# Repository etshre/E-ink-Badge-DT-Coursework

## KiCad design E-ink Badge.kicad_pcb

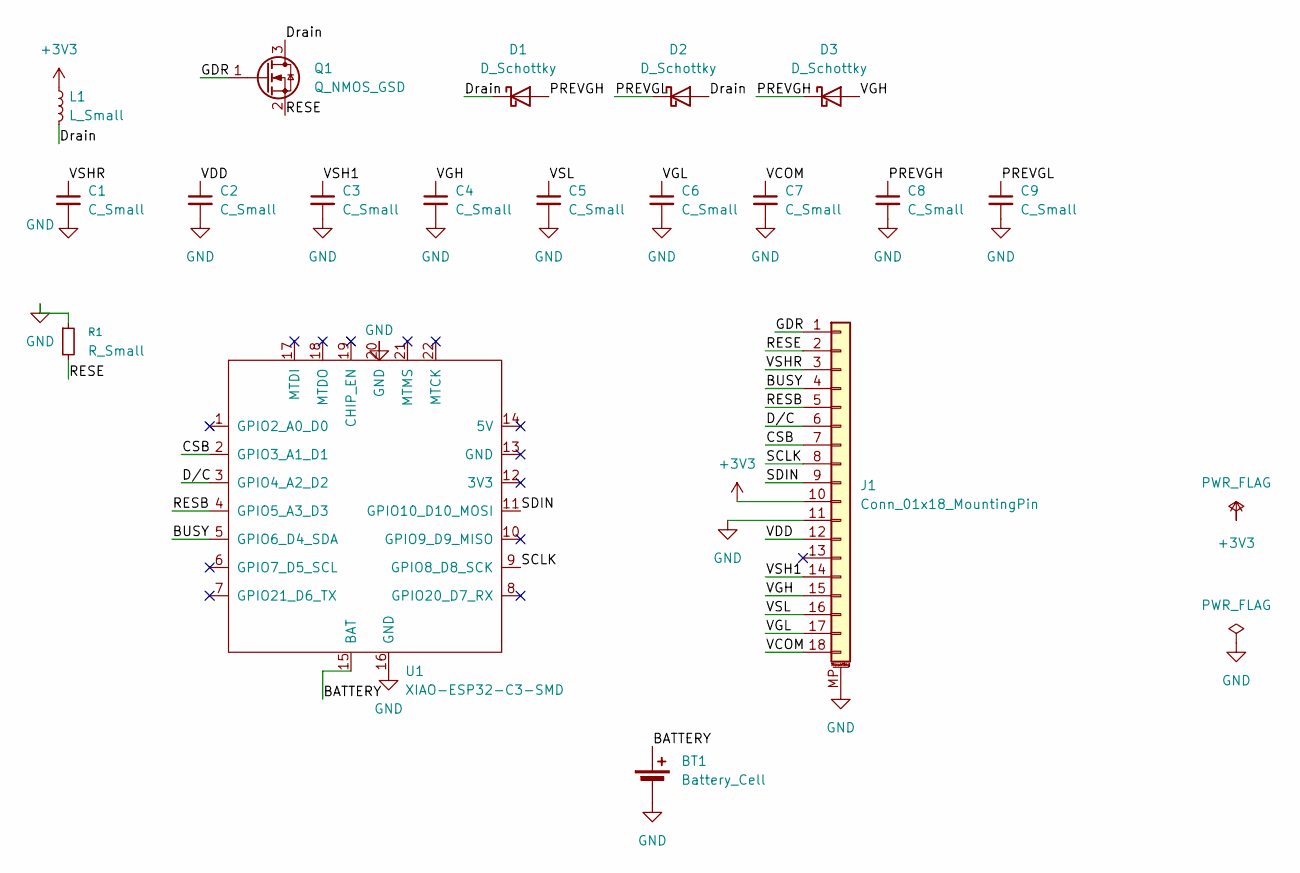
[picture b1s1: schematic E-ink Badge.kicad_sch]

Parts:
BT1: Battery_Cell; PinHeader_1x02_P2.54mm_Vertical
C1, C2, C3, C4, C5, C6, C7, C8, C9: C_Small; C_0805_2012Metric_Pad1.18x1.45mm_HandSolder
D1, D2, D3: D_Schottky; D_SOD-123
J1: Conn_01x18_MountingPin; Hirose_FH12-18S-0.5SH_1x18-1MP_P0.50mm_Horizontal
L1: L_Small; L_Wuerth_MAPI-3015
Q1: Q_NMOS_GSD; SOT-23_Handsoldering
R1: R_Small; R_0805_2012Metric_Pad1.20x1.40mm_HandSolder
U1: XIAO-ESP32-C3-SMD

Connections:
+3V3: J1.10, L1.1
/BATTERY: BT1.1 (+), U1.15 (BAT)
/BUSY: J1.4, U1.5 (GPIO6_D4_SDA)
/CSB: J1.7, U1.2 (GPIO3_A1_D1)
/Drain: D1.1 (K), D2.2 (A), L1.2, Q1.3 (D)
/D/C: J1.6, U1.3 (GPIO4_A2_D2)
/GDR: J1.1, Q1.1 (G)
/PREVGH: C8.1, D1.2 (A), D3.1 (K)
/PREVGL: C9.1, D2.1 (K)
/RESB: J1.5, U1.4 (GPIO5_A3_D3)
/RESE: J1.2, Q1.2 (S), R1.2
/SCLK: J1.8, U1.9 (GPIO8_D8_SCK)
/SDIN: J1.9, U1.11 (GPIO10_D10_MOSI)
/VCOM: C7.1, J1.18
/VDD: C2.1, J1.12
/VGH: C4.1, D3.2 (A), J1.15
/VGL: C6.1, J1.17
/VSH1: C3.1, J1.14
/VSHR: C1.1, J1.3
/VSL: C5.1, J1.16
GND: BT1.2 (-), C1.2, C2.2, C3.2, C4.2, C5.2, C6.2, C7.2, C8.2, C9.2, J1.11, J1.MP (MountPin), R1.1, U1.16 (GND), U1.20 (GND)

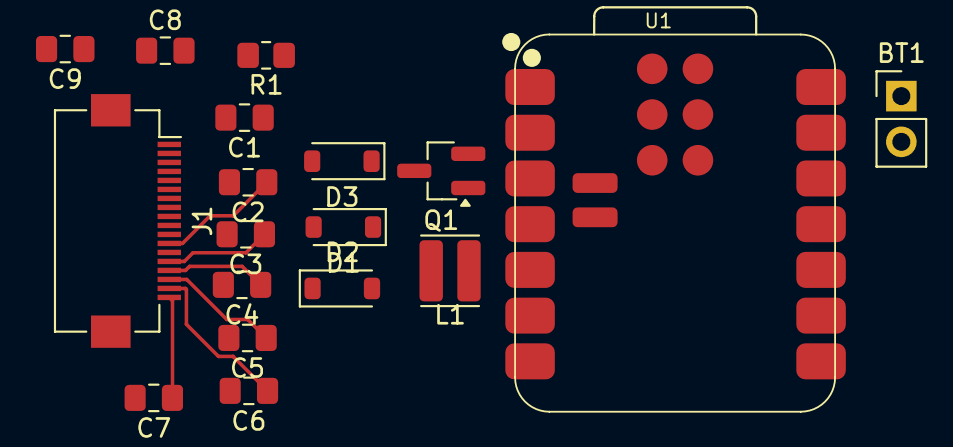
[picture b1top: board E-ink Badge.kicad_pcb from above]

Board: 2 copper layers, 18 parts (0 on the bottom side), 21 nets.
